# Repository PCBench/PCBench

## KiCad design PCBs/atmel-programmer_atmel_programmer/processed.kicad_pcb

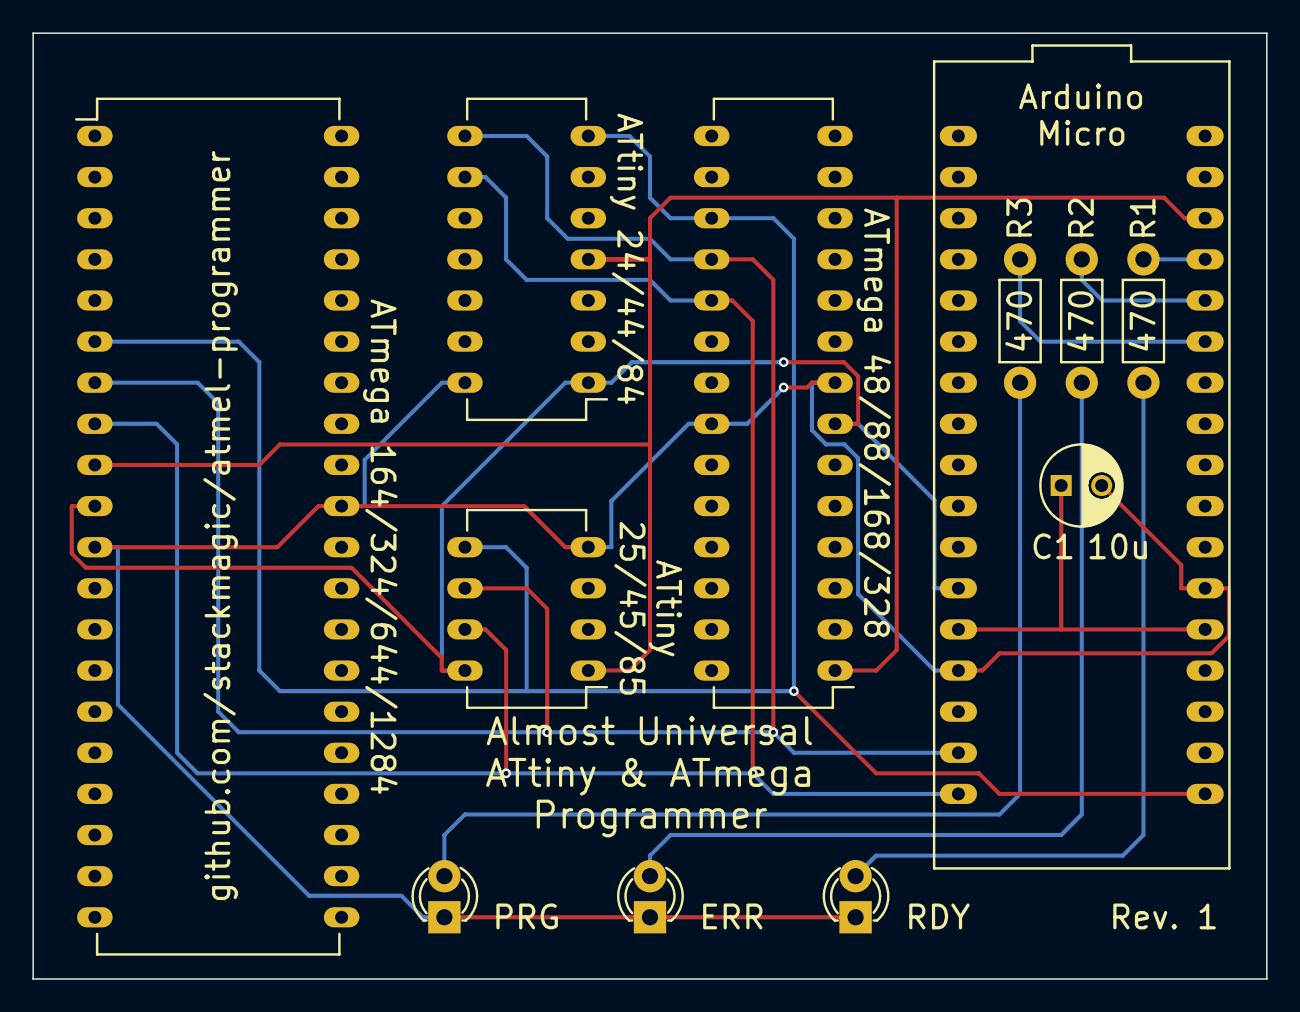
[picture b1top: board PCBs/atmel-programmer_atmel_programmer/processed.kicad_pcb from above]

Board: 2 copper layers, 76.2 x 58.4 mm, 12 parts (0 on the bottom side), 13 nets.

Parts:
C1: 10u; C_Radial_D5_L6_P2.5
D1, D2, D3: LED; LED-3MM
IC1: ATTINY85-P; DIP-8_W7.62mm_LongPads
IC2: ATTINY84-P; DIP-14_W7.62mm_LongPads
IC3: ATMEGA328-P; DIP-28_W7.62mm_LongPads
IC4: ATMEGA1284-P; DIP-40_W15.24mm_LongPads
R1, R2, R3: 470; Resistor_Horizontal_RM7mm
U1: Arduino_Micro_ISP; ArduinoMicro

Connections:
GND: C1.2, D1.1, D2.1, D3.1, IC1.4, IC2.14, IC3.8, IC3.22, IC4.11, IC4.31, U1.14, U1.23
MISO: IC1.6, IC2.8, IC3.18, IC4.7, U1.16
MOSI: IC1.5, IC2.7, IC3.17, IC4.6, U1.18
unnamed: C1.1, U1.13, U1.22
unnamed: D1.2, R1.1
unnamed: D2.2, R2.1
unnamed: D3.2, R3.1
unnamed: R1.2, U1.31
unnamed: R2.2, U1.30
unnamed: R3.2, U1.29
RST: IC1.1, IC2.4, IC3.1, IC4.9, U1.32
SCK: IC1.7, IC2.9, IC3.19, IC4.8, U1.17
VCC: IC1.8, IC2.1, IC3.7, IC4.10, U1.12

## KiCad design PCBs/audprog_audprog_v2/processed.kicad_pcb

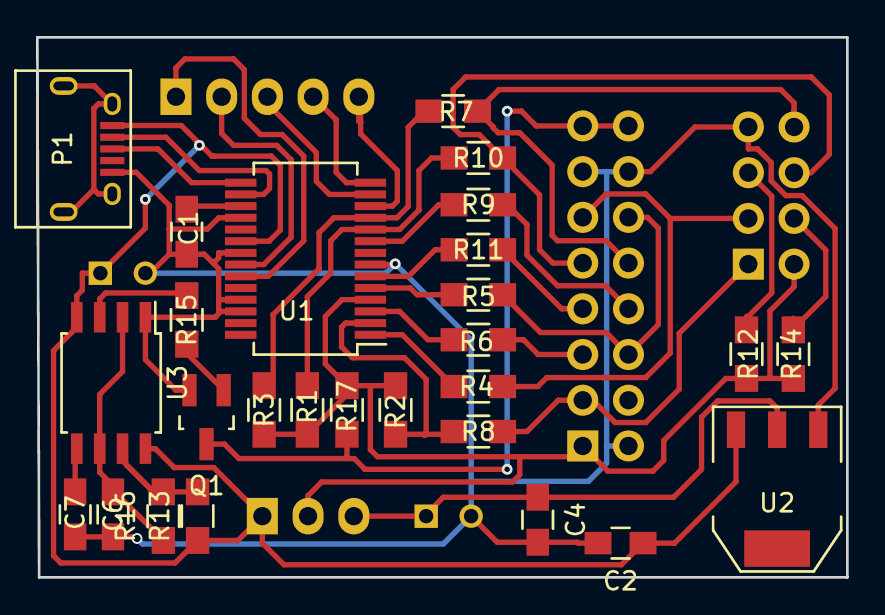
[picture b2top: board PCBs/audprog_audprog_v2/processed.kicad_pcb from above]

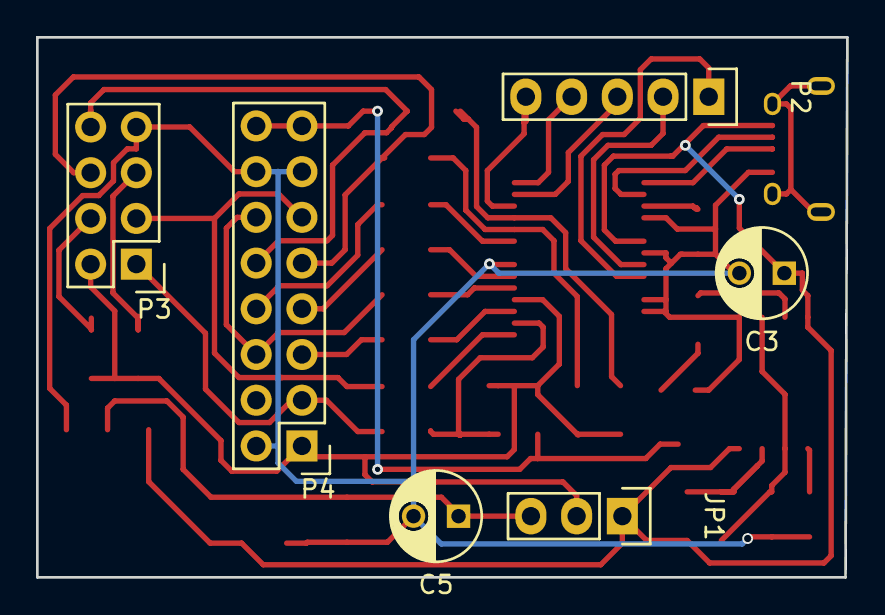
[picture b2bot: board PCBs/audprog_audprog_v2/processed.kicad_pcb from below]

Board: 2 copper layers, 45.0 x 30.0 mm, 33 parts (6 on the bottom side), 36 nets.

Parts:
C1, C6: 100n; C_0805_HandSoldering
C2, C4: 0,1u; C_0805_HandSoldering
C3, C5: 470u; C_Radial_D5_L11_P2.5
C7: 10n; C_0805_HandSoldering
JP1: Vcc_IO_SW; Pin_Header_Straight_1x03
P1: USB_OTG; USB_Micro-B
P2: CONN_01X05; Pin_Header_Straight_1x05
P3: CONN_02X04; Pin_Header_Straight_2x04
P4: CONN_02X08; Pin_Header_Straight_2x08
Q1: BC817; SOT-23_Handsoldering
R1, R2, R3: 5,6k; R_0805_HandSoldering
R4, R5, R6, R7, R8, R9, R10, R11: 22; R_0805_HandSoldering
R12, R14, R15, R17: 10k; R_0805_HandSoldering
R13: 1k; R_0805_HandSoldering
R16: 47,5k; R_0805_HandSoldering
U1: FT232RL; SSOP-28_5.3x10.2mm_Pitch0.65mm
U2: AP1117E33; SOT-223
U3: LM555N; SOIJ-8_5.3x5.3mm_Pitch1.27mm

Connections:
+3V3: C4.1, C5.1, JP1.3, U2.2
+5V: C2.1, C3.1, JP1.1, P1.1, R13.1, U1.20, U2.3, U3.4, U3.8
AUD_CK: P3.6, P4.9, R10.1
AUD_DATA0: P4.5, R6.1
AUD_DATA1: P4.6, P4.12, R5.1
AUD_DATA2: P4.7, R11.1
AUD_DATA3: P4.8, R9.1
AUD_RST: P3.1, P4.3, R8.1
AUD_SYNC: P3.8, P4.10, R7.1
BOOT_TX: P3.3, P4.11, R4.1
CBUS1: P2.1, U1.23
CBUS2: P2.2, U1.22
CBUS3: P2.3, U1.13
CBUS4: P2.4, U1.14
CBUS5: P2.5, U1.12
GND: C1.2, C2.2, C3.2, C4.2, C5.2, C6.2, C7.2, P1.5, P3.7, P4.2, P4.13, P4.14, Q1.2, U1.7, U1.18, U1.21, U1.25, U1.26, U2.1, U3.1
unnamed: C1.1, U1.17
unnamed: C6.1, R16.1, U3.2, U3.6
unnamed: C7.1, U3.5
unnamed: P1.2, U1.16
unnamed: P1.3, U1.15
unnamed: P3.4, R14.2
unnamed: P3.5, R12.1
unnamed: Q1.1, R15.1
unnamed: R1.2, R10.2, U1.10
unnamed: R2.2, R8.2, U1.2
unnamed: R3.2, R7.2, U1.11
unnamed: R4.2, U1.1
unnamed: R5.2, U1.5
unnamed: R6.2, U1.3
unnamed: R9.2, U1.9
unnamed: R11.2, U1.6
unnamed: R13.2, R16.2, U3.7
unnamed: R15.2, U3.3
VCC_IO: JP1.2, P3.2, P4.1, R1.1, R2.1, R3.1, R12.2, R14.1, R17.1, U1.4
WDT: P4.15, P4.16, Q1.3, R17.2

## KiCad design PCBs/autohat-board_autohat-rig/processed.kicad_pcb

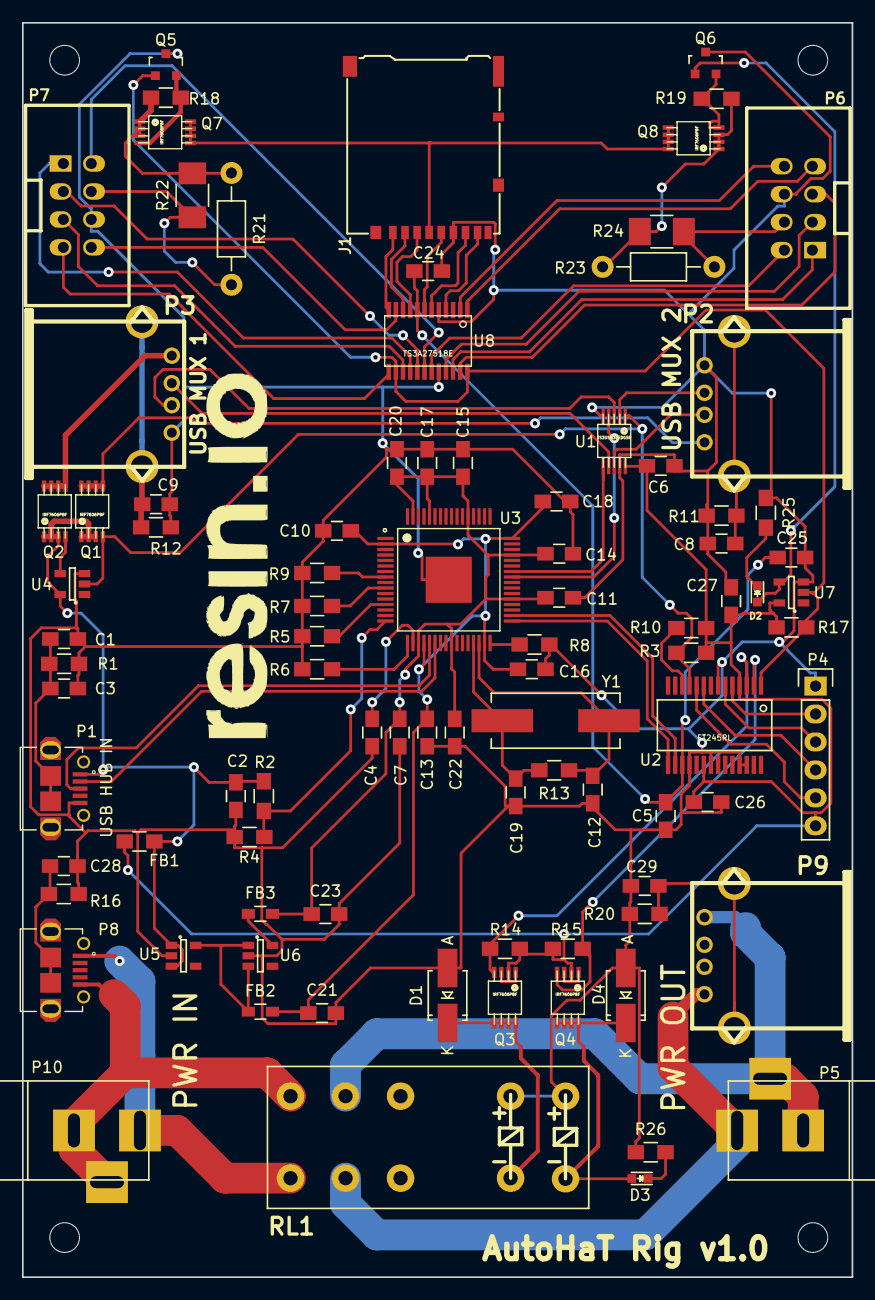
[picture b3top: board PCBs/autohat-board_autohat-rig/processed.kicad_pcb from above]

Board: 2 copper layers, 75.4 x 114.0 mm, 91 parts (0 on the bottom side), 78 nets.

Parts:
C1, C5, C6, C7, C10, C11, C13, C14, C15, C16, C17, C18, C20, C22, C24, C25, C26: 100n; C_0805_HandSoldering
C2, C21, C23: 10u; C_0805_HandSoldering
C3: 1n; C_0805_HandSoldering
C4: 1u; C_0805_HandSoldering
C8, C9, C28, C29: 27p; C_0805_HandSoldering
C12, C19: 18p; C_0805_HandSoldering
C27: 4.7u; C_0805_HandSoldering
D1, D4: ES1A-LTP; SMA_Handsoldering
D2, D3: LED; LED_0603
FB1: MI0805K400R-10; R_0805_HandSoldering
FB2, FB3: BLM18PG221SN1D; R_0603_HandSoldering
J1: USDCARD; HIROSE-MICROSD-DM3AT-SF
P1: USB HUB IN; TO_microUSB
P2: USB MUX 2; conn_usb_A
P3: USB MUX 1; conn_usb_A
P4: CONN_01X06; Pin_Header_Straight_1x06
P5, P10: BARREL_JACK
P6, P7: IDC_02X04; PSB_IDC_4x2
P8: PWR IN; TO_microUSB
P9: PWR OUT; conn_usb_A
Q1, Q2, Q3, Q4, Q7, Q8: IRF7606PBF; msoic-8
Q5, Q6: 2N7002; SOT-23
R1, R13: 1M; R_0805_HandSoldering
R2: 90.9K; R_0805_HandSoldering
R3, R4, R10, R14, R15, R17, R18, R19, R25, R26: 10K; R_0805_HandSoldering
R5, R6, R7, R9, R11, R12, R16, R20: 4.7K; R_0805_HandSoldering
R8: 9.53K; R_0805_HandSoldering
R21, R23: 0; Resistor_Horizontal_RM10mm
R22, R24: 0; R_1210_HandSoldering
RL1: G2RK-2-DC5; G2RK-2
U1: TS3USB30EDGSR; msoic-10
U2: FT245RL; ssop-28
U3: TUSB4041IPAPR; QFP50P1200X1200X105-65N
U4, U7: 74AHC1G14; SOT-23-5
U5: TLV73333; SOT-23-5
U6: TLV73311; SOT-23-5
U8: TS3A27518E; tssop-24
Y1: 24MHz; Crystal_HC49-SD_SMD

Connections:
+3V3: C5.1, C24.1, C25.1, U2.17, U8.8
/1P1V: FB3.1, U6.5
/3P3V: FB2.1, U5.5, U6.1, U6.3
/CLK_DUT: P6.5, U8.23
/CLK_TS: P7.5, U8.15
/CMD_DUT: P6.3, U8.21
/CMD_TS: P7.3, U8.17
/DAT0_DUT: P6.7, U8.1
/DAT0_TS: P7.7, U8.13
/DAT1_DUT: P6.8, U8.2
/DAT1_TS: P7.8, U8.11
/DAT2_DUT: P6.1, U8.22
/DAT2_TS: P7.1, U8.16
/DAT3_DUT: P6.2, U8.19
/DAT3_TS: P7.2, U8.18
/POWER_SW_OFF: Q3.4, R14.2, U2.3
/POWER_SW_ON: Q4.4, R15.2, U2.2
/SOCKET_SEL: Q5.1, R17.2, U2.1, U7.2, U8.14, U8.24
/USB_DN1+: U2.15, U3.33
/USB_DN1-: U2.16, U3.34
/USB_DN2+: U1.4, U3.41
/USB_DN2-: U1.6, U3.42
/USB_MUX1+: P2.3, U1.2
/USB_MUX1-: P2.2, U1.8
/USB_MUX2+: P3.3, U1.3
/USB_MUX2-: P3.2, U1.7
/USB_SEL: Q1.4, R3.2, U1.1, U2.11, U4.2
/USB_UP+: P1.3, U3.21
/USB_UP-: P1.2, U3.22
/USB_VBUS: C2.1, FB1.2, P1.1, Q1.1, Q1.2, Q1.3, Q2.1, Q2.2, Q2.3, R2.1, U4.5, U5.1, U5.3
/USD_VDD: J1.4, Q7.5, Q7.6, Q7.7, Q7.8, Q8.5, Q8.6, Q8.7, Q8.8
/VDD_DUT: P6.4, R23.1, R24.1
/VDD_TS: P7.4, R21.1, R22.1
/XI: C12.1, R13.1, U3.30, Y1.1
/XO: C19.1, R13.2, U3.29, Y1.2
GND: C1.2, C2.2, C3.2, C4.1, C5.2, C6.2, C7.2, C8.2, C9.2, C10.2, C11.2, C12.2, C13.2, C14.2, C15.2, C16.2, C17.2, C18.2, C19.2, C20.2, C21.2, C22.2, C23.2, C24.2, C25.2, C26.2, C27.2, C28.2, C29.2, D1.2, D4.2, J1.6, P1.5, P2.4, P3.4, P4.1, P6.6, P7.6, Q5.3, Q6.3, R1.1, R4.1, R5.1, R6.1, R7.1, R8.1, R9.1, R11.2, R12.2, R16.2, R20.2, R25.1, R26.1, RL1.9, RL1.10, U1.5, U1.9, U2.7, U2.18, U2.21, U2.25, U2.26, U3.65, U4.3, U5.2, U6.2, U7.3, U8.5, U8.20
unnamed: C1.1, C3.1, P1.6, R1.2
unnamed: C4.2, U3.18
unnamed: C8.1, P2.5, R11.1
unnamed: C9.1, P3.5, R12.1
unnamed: C10.1, C13.1, C16.1, C18.1, C21.1, FB2.2, U3.2, U3.20, U3.31, U3.48
unnamed: C7.1, C11.1, C14.1, C15.1, C17.1, C20.1, C22.1, C23.1, FB3.2, U3.19, U3.25, U3.37, U3.45, U3.53, U3.60, U3.63
unnamed: C28.1, P8.6, R16.1
unnamed: C29.1, P9.5, R20.1
unnamed: D1.1, Q3.5, Q3.6, Q3.7, Q3.8, RL1.2
unnamed: D2.1, R25.2
unnamed: D2.2, Q6.1, U7.4
unnamed: D3.1, R26.2
unnamed: D3.2, D4.1, Q4.5, Q4.6, Q4.7, Q4.8, RL1.1
unnamed: J1.1, U8.12
unnamed: J1.2, U8.10
unnamed: J1.3, U8.9
unnamed: J1.5, U8.7
unnamed: J1.7, U8.6
unnamed: J1.8, U8.4
unnamed: P2.1, Q1.5, Q1.6, Q1.7, Q1.8
unnamed: P3.1, Q2.5, Q2.6, Q2.7, Q2.8
unnamed: P4.2, U2.5
unnamed: P4.3, U2.6
unnamed: P4.4, U2.9
unnamed: P4.5, U2.10
unnamed: P5.1, P9.1, RL1.4
unnamed: P5.2, P5.3, P9.4, RL1.7
unnamed: P8.1, P10.1, RL1.5
unnamed: P8.5, P10.2, P10.3, RL1.6
unnamed: Q2.4, U4.4
unnamed: Q5.2, Q7.4, R18.2
unnamed: Q6.2, Q8.4, R19.2
unnamed: Q7.1, Q7.2, Q7.3, R18.1, R21.2, R22.2
unnamed: Q8.1, Q8.2, Q8.3, R19.1, R23.2, R24.2
unnamed: R2.2, R4.2, U3.16
unnamed: R5.2, U3.13
unnamed: R6.2, U3.17
unnamed: R7.2, U3.10
unnamed: R8.2, U3.32
unnamed: R9.2, U3.8
unnamed: R10.2, U2.12
VDD: C6.1, C26.1, C27.1, FB1.1, P4.6, Q3.1, Q3.2, Q3.3, Q4.1, Q4.2, Q4.3, R3.1, R10.1, R14.1, R15.1, R17.1, U1.10, U2.4, U2.20, U7.5

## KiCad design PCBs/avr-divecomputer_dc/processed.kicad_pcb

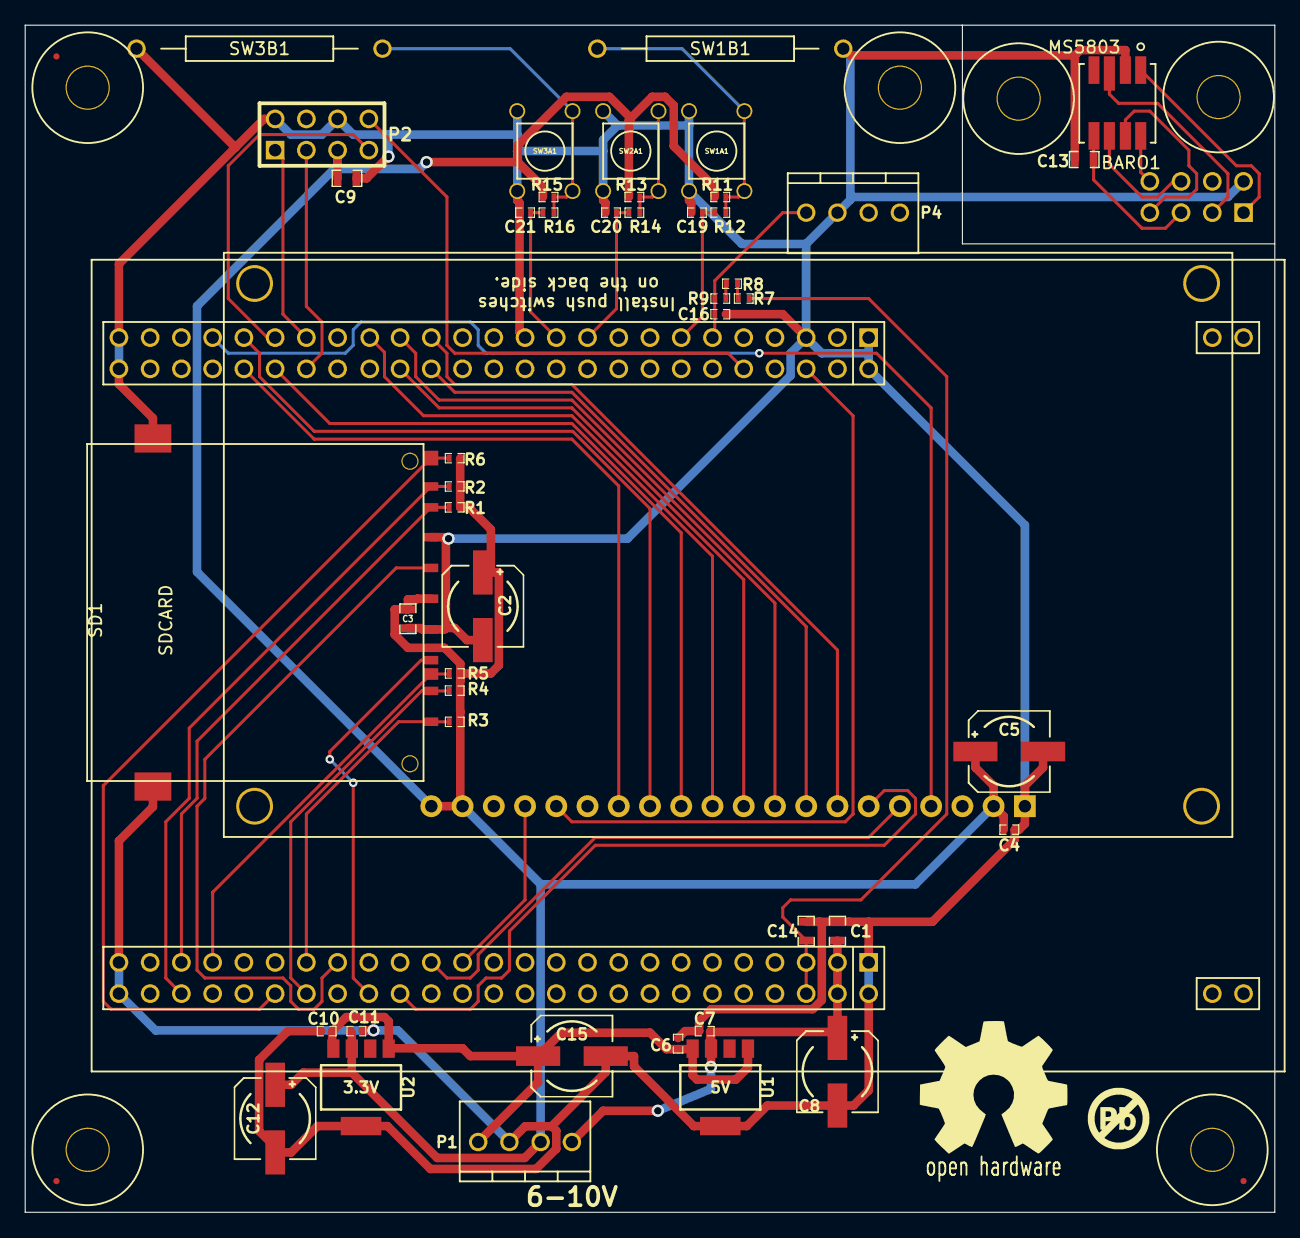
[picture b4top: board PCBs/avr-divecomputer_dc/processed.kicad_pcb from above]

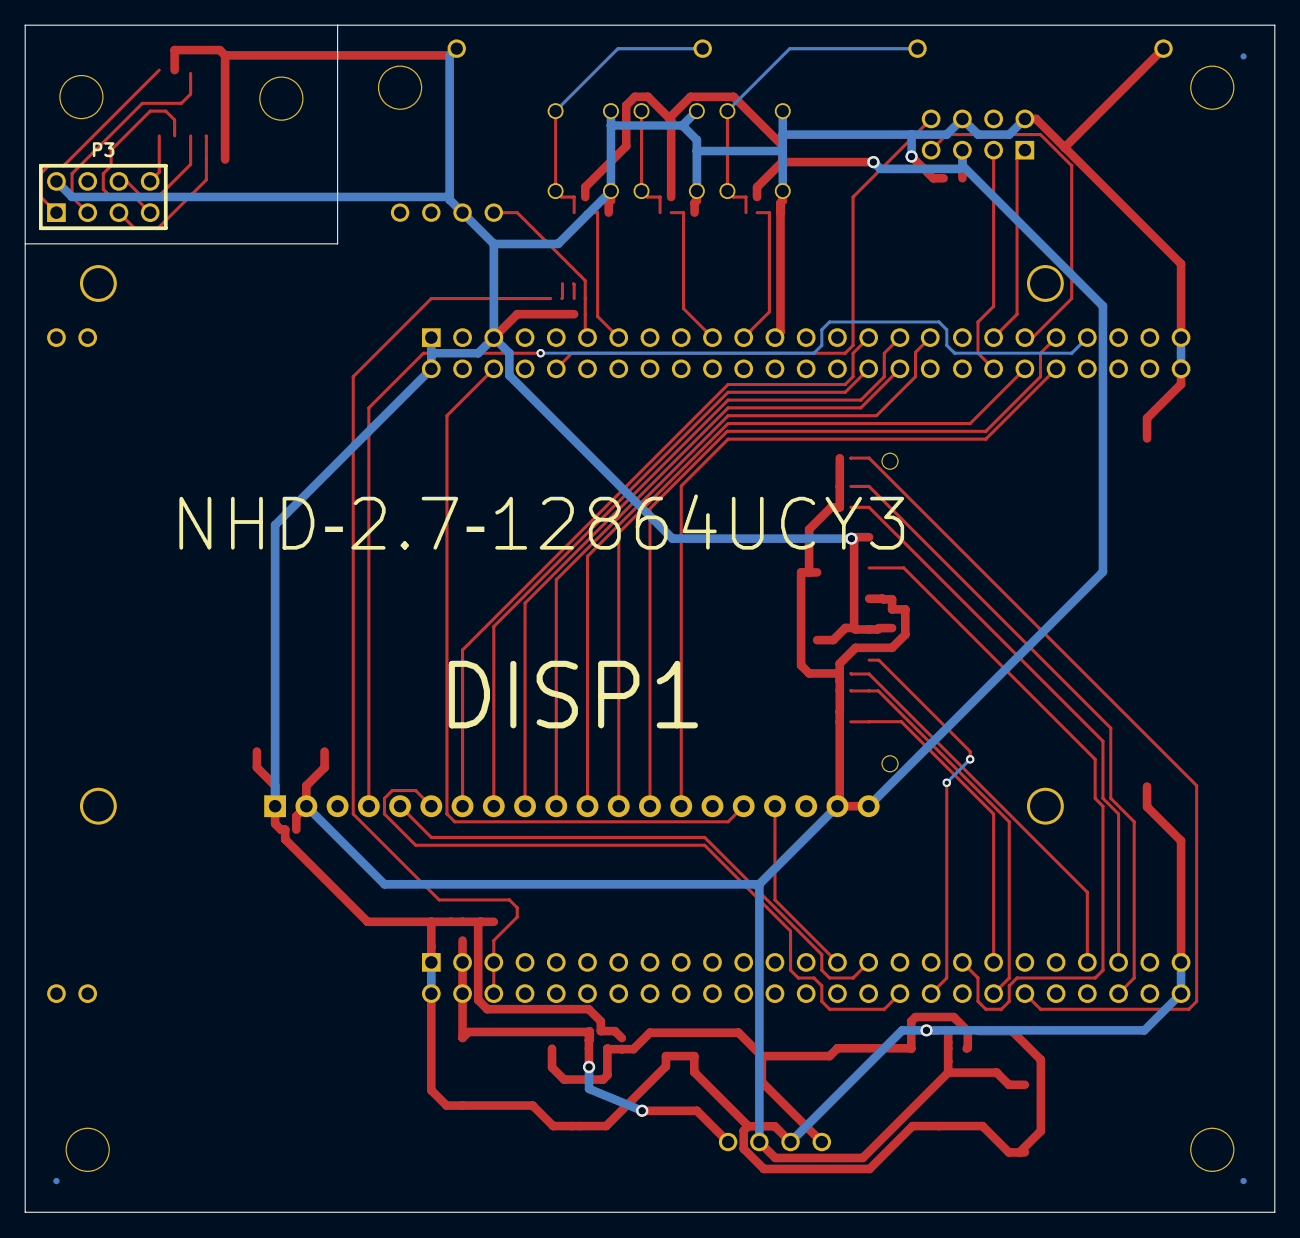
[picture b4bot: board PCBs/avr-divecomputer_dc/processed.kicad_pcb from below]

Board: 2 copper layers, 101.6 x 96.5 mm, 58 parts (2 on the bottom side), 45 nets.

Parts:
BARO1: MS5803
C1, C3, C9, C13, C14: 10uF; SM0603_Capa
C2, C5, C8, C12, C15: 150uF; c_elec_6.3x5.7
C4, C6, C7, C10, C11, C16, C19, C20, C21: 1uF; SM0402_c
DISP1: NHD‐2.7‐12864UCY3
FID1: FID**; FIDUCIAL
FID2, FID3: VAL**; FIDUCIAL
J1: STM32F4_DISCOVERY_HEADER; stm32f4_discovery_header
M3_MOUNT, M3_MOUNT_2, M3_MOUNT_3, M3_MOUNT_4, M3_MOUNT_5, M3_MOUNT_6: VAL**; M3_MOUNT
P1, P4: CONN_4; ED10563-ND
P2, P3: CONN_4X2; pin_array_4x2
R1, R2, R3, R4, R5, R6, R7, R8, R9, R11, R12, R13, R14, R15, R16: 100k; SM0402
SD1: SDCARD; 101-00405-75-ND
SW1A1, SW2A1, SW3A1: SW_PUSH; P8008S-ND
SW1B1, SW3B1: SW_PUSH; REED
U1: 5V; SOT-223-5
U2: 3.3V; SOT-223-5

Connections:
+3.3V: C2.1, C3.1, C4.1, C5.1, C9.1, C11.1, C12.1, DISP1.2, DISP1.19, DISP1.20, P1.3, P2.5, R1.1, R2.1, R3.1, R4.1, R5.2, R6.2, R11.2, R13.2, R15.2, SD1.4, U2.3
+5V: C1.1, C7.1, C8.1, J1.97, J1.98, P1.4, U1.3
+BATT: C6.1, C10.1, C15.1, P1.1, U1.1, U1.4, U2.1, U2.4
DEPTH_CS: J1.38, P2.3
FSMC_A16: DISP1.4, J1.43
FSMC_D08: DISP1.7, J1.29
FSMC_D09: DISP1.8, J1.30
FSMC_D10: DISP1.9, J1.31
FSMC_D11: DISP1.10, J1.32
FSMC_D12: DISP1.11, J1.33
FSMC_D13: DISP1.12, J1.40
FSMC_D14: DISP1.13, J1.41
FSMC_D15: DISP1.14, J1.42
FSMC_NE1: DISP1.17, J1.73
FSMC_NOE: DISP1.6, J1.70
FSMC_NWE: DISP1.5, J1.71
GND: BARO1.2, C1.2, C2.2, C3.2, C4.2, C5.2, C6.2, C7.2, C8.2, C9.2, C10.2, C11.2, C12.2, C13.2, C14.2, C15.2, C16.2, C19.2, C20.2, C21.2, DISP1.1, J1.1, J1.2, J1.5, J1.23, J1.49, J1.50, J1.51, J1.52, J1.99, J1.100, P1.2, P2.2, P2.6, P3.2, P4.3, SD1.3, SD1.6, SD1.10, SW1A1.1, SW1B1.1, SW2A1.1, SW3A1.1, SW3B1.1, U1.5, U2.5
unnamed: R11.1, R12.1, SW1A1.2, SW1B1.2
unnamed: R7.1, R8.2
unnamed: R8.1, R9.1
unnamed: R13.1, R14.1, SW2A1.2
unnamed: R15.1, R16.1, SW3A1.2, SW3B1.2
unnamed: BARO1.8, P3.8
unnamed: BARO1.7, P3.7
unnamed: BARO1.6, P3.6
unnamed: BARO1.5, C13.1, P3.5
unnamed: BARO1.1, P3.1
unnamed: BARO1.3, P3.3
RESET: DISP1.16, J1.6
SDIO_CK: J1.65, SD1.5
SDIO_CMD: J1.68, SD1.2
SDIO_D0: J1.55, R1.2, SD1.7
SDIO_D1: J1.56, R2.2, SD1.8
SDIO_D2: J1.63, R3.2, SD1.9
SDIO_D3: J1.64, R4.2, SD1.1
SD_CD: J1.57, R5.1, SD1.11
SD_WP: J1.62, R6.1, SD1.12
SPI2_MISO: J1.10, P2.8
SPI2_MOSI: J1.39, P2.7
SPI2_SCK: J1.37, P2.1
STM_3V: C14.1, J1.95, J1.96, R7.2
SW1: C19.1, J1.13, R12.2
SW2: C20.1, J1.19, R14.2
SW3: C21.1, J1.21, R16.2
WATER: C16.1, J1.11, P4.4, R9.2

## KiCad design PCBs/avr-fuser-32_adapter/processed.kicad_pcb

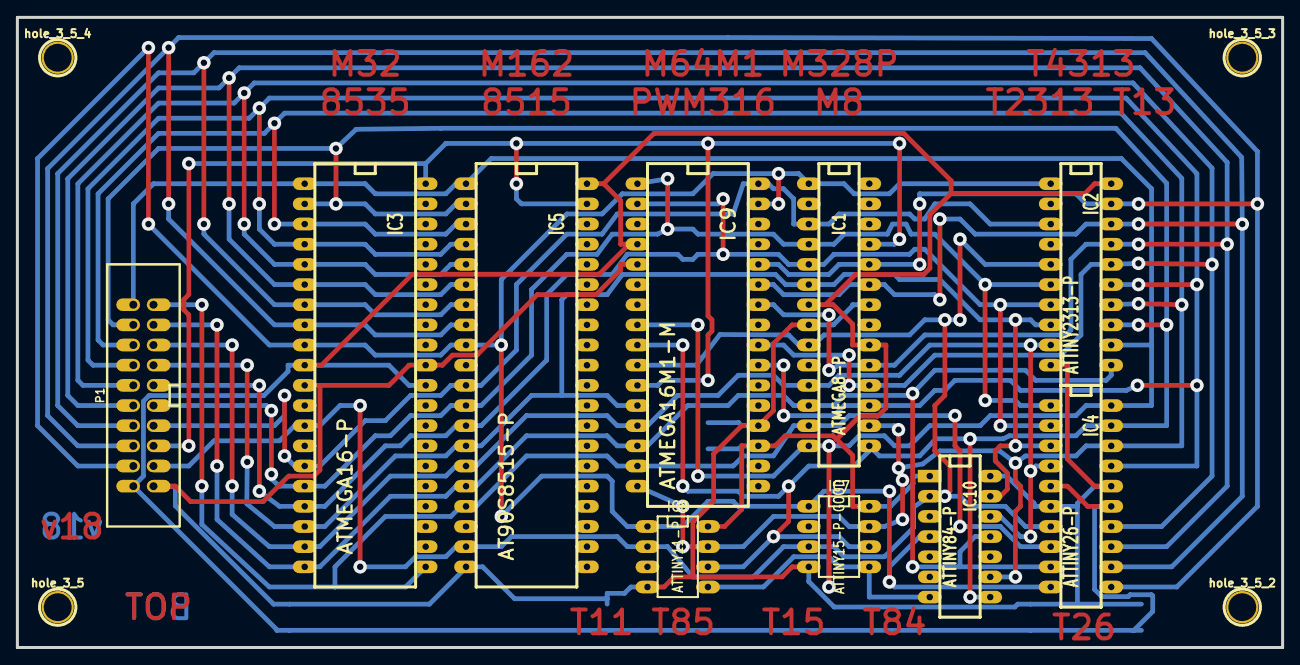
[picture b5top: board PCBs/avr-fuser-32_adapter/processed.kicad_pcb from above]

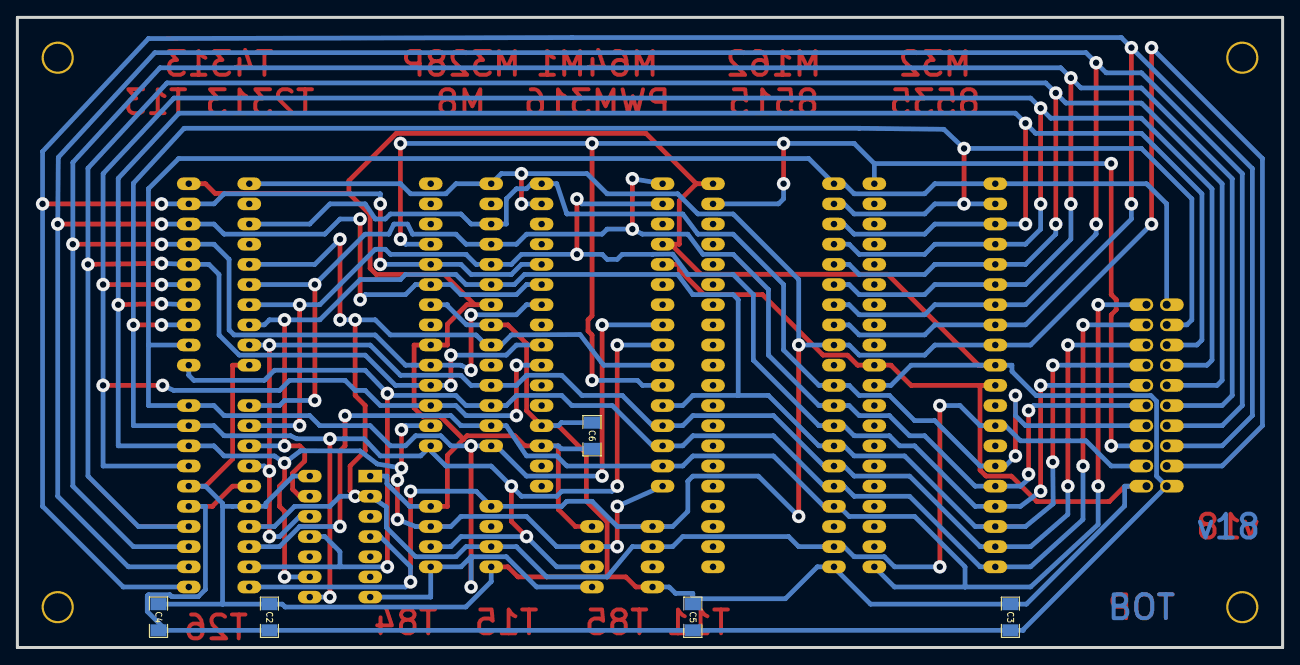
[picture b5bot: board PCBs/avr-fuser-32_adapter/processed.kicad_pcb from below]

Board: 2 copper layers, 159.4 x 79.4 mm, 19 parts (5 on the bottom side), 20 nets.

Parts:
C2, C3, C4, C5, C6: 10nF; SM1206
IC1: ATMEGA8-P; DIP-28__300-bigpads
IC2: ATTINY2313-P; DIP-20__300-bigpads
IC3: ATMEGA16-P; DIP-40__600-bigpads
IC4: ATTINY26-P; DIP-20__300-bigpads
IC5: AT90S8515-P; DIP-40__600-bigpads
IC7: ATTINY15-P-GOOD; DIP-8__300-bigpads
IC8: ATTINY11-P; DIP-8__300-bigpads
IC9: ATMEGA16M1-M; DIP-32__600_bigpads
IC10: ATTINY84-P; DIP-14__300_ELL-bigpads
P1: CONN_10X2; conn_strip_10x2_largepads
hole_3_5, hole_3_5_2, hole_3_5_3, hole_3_5_4: 3.5mm; hole_3_5

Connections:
/BS1: IC1.6, IC2.8, IC3.18, IC4.3, IC5.14, IC9.12, IC10.13, P1.13
/BS2: IC1.25, IC3.40, IC5.39, IC9.11, P1.5
/CLK: IC1.9, IC2.5, IC3.13, IC4.7, IC5.19, IC7.3, IC8.2, IC9.10, IC10.2, P1.3
/D0: IC1.14, IC2.12, IC3.1, IC4.20, IC5.1, IC7.5, IC8.5, IC9.8, IC10.7, P1.20
/D1: IC1.15, IC2.13, IC3.2, IC4.19, IC5.2, IC7.6, IC8.6, IC9.9, IC10.8, P1.18
/D2: IC1.16, IC2.14, IC3.3, IC4.18, IC5.3, IC7.7, IC8.7, IC9.16, IC10.9, P1.16
/D3: IC1.17, IC2.15, IC3.4, IC4.17, IC5.4, IC9.23, P1.14
/D4: IC1.18, IC2.16, IC3.5, IC4.14, IC5.5, IC9.24, P1.12
/D5: IC1.19, IC2.17, IC3.6, IC4.13, IC5.6, IC9.26, P1.10
/D6: IC1.23, IC2.18, IC3.7, IC4.12, IC5.7, IC9.27, P1.8
/D7: IC1.24, IC2.19, IC3.8, IC4.11, IC5.8, IC9.28, P1.6
/OE: IC1.4, IC2.6, IC3.16, IC4.1, IC5.12, IC9.1, P1.9
/PAGEL: IC1.13, IC3.21, IC4.8, IC5.17, IC9.15, P1.19
/RDY: IC1.3, IC2.3, IC3.15, IC5.11, IC9.32, P1.7
/RST12V: IC1.1, IC2.1, IC3.9, IC4.10, IC5.9, IC7.1, IC8.1, IC9.31, IC10.4, P1.4
/VCC: C2.1, C3.1, C4.1, C5.1, C6.1, IC1.7, IC1.20, IC2.20, IC3.10, IC3.30, IC4.5, IC4.15, IC5.40, IC7.8, IC8.8, IC9.4, IC9.19, IC10.1, P1.2
/WR: IC1.5, IC2.7, IC3.17, IC4.2, IC5.13, IC9.2, P1.11
/XA0: IC1.11, IC2.9, IC3.19, IC4.4, IC5.15, IC9.13, IC10.12, P1.15
/XA1: IC1.12, IC2.11, IC3.20, IC4.9, IC5.16, IC9.14, IC10.11, P1.17
GND: C2.2, C3.2, C4.2, C5.2, C6.2, IC1.8, IC1.22, IC2.10, IC3.11, IC3.31, IC4.6, IC4.16, IC5.20, IC7.4, IC8.4, IC9.5, IC9.20, IC10.14, P1.1

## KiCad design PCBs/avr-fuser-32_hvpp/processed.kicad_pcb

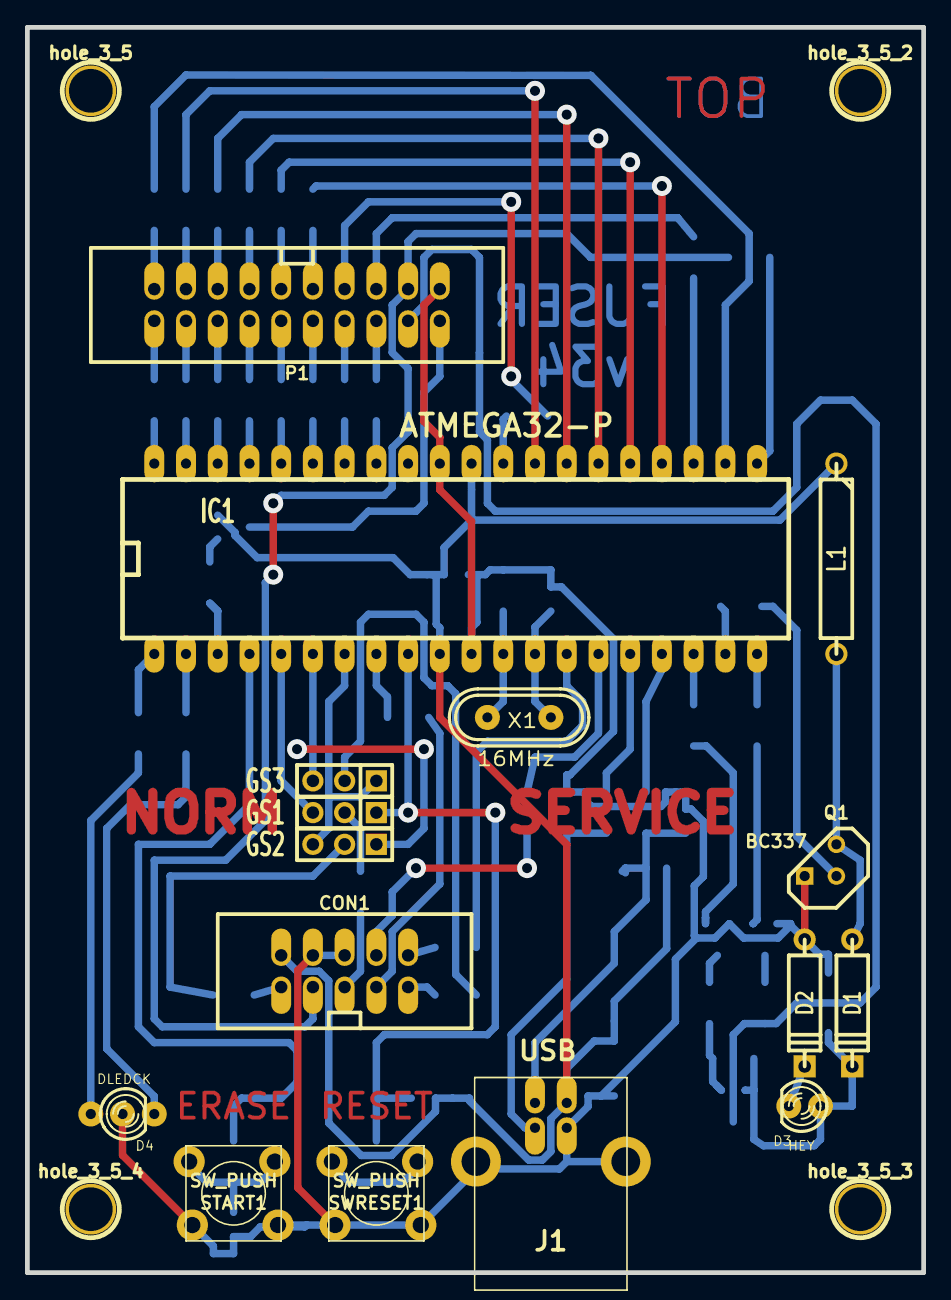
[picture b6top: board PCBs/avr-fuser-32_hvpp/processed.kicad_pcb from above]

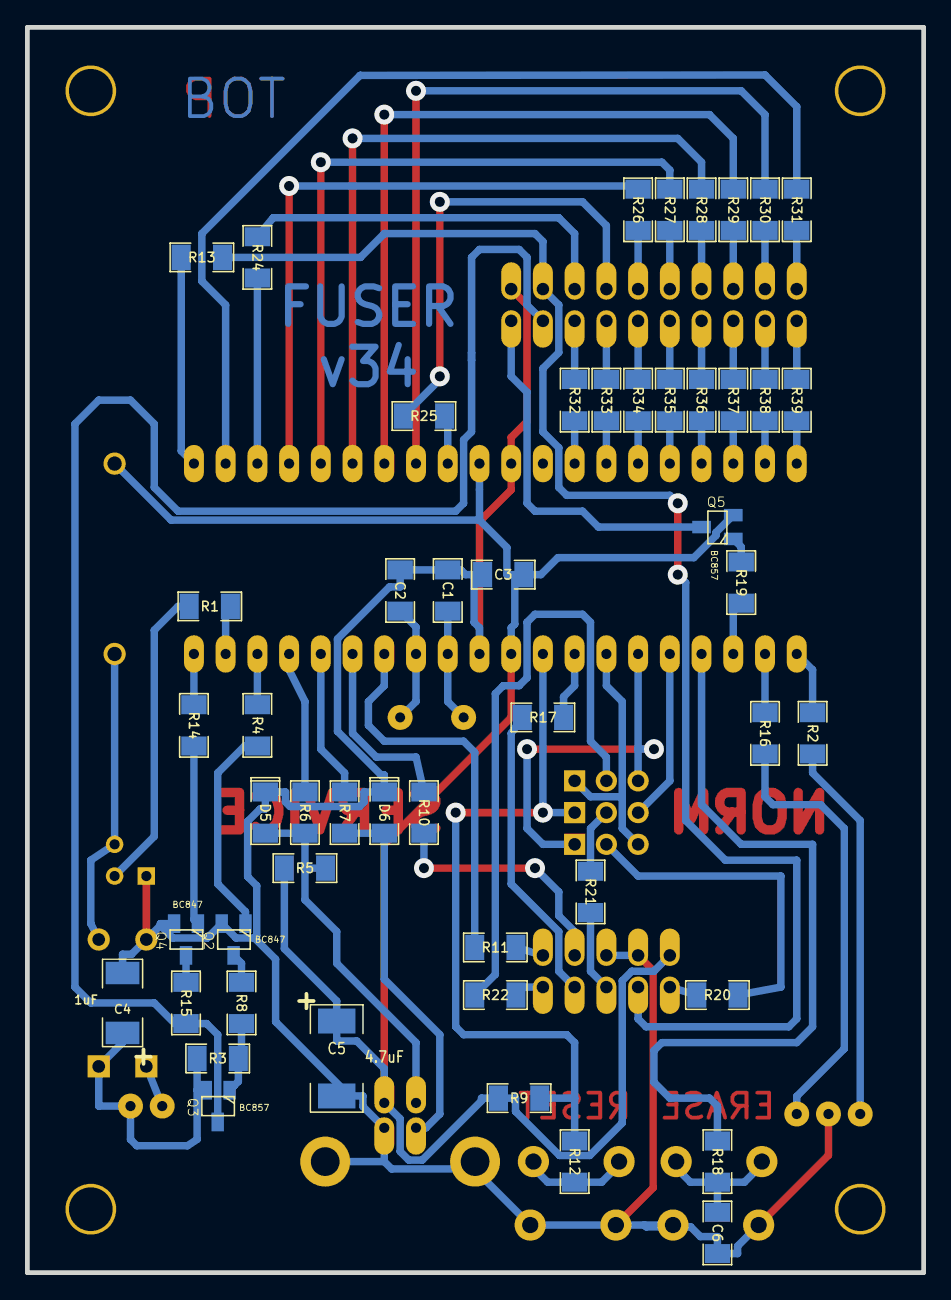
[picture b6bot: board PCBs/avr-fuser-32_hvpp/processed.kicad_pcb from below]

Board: 2 copper layers, 71.8 x 99.7 mm, 70 parts (50 on the bottom side), 81 nets.

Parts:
C1, C2: 18pF; SM1206
C3: 56nF; SM1206
C4: 1uF; SM2010
C5: 4.7uF; SM2512
C6: 1nF; SM1206
CON1: AVR-ISP-10; conn_strip_5x2_largepads
D1: BAT42; D4
D2: 10V; D4
D3: HEY; LED-3MM-bigpads
D4: DLEDCK; LED-3MM-dual-bigpads
D5, D6: 3.6V; SM1206POL
GS1, GS2, GS3: GS3; SIL-3_bigpads
IC1: ATMEGA32-P; DIP-40__600-bigpads
J1: USB; USB_B-bigpads
L1: 220uH; R6
P1: CONN_10X2; conn_strip_10x2_largepads
Q1: BC337; TO92
Q2, Q4: BC847; SOT23_INV-bigpads
Q3, Q5: BC857; SOT23_INV-bigpads
R1: 9.1k; SM1206
R2, R4, R14, R16, R19: 1k; SM1206
R3: 100k; SM1206
R5: 2.2k; SM1206
R6, R7: 68; SM1206
R8: 4.7k; SM1206
R9: 15k; SM1206
R10, R11, R13, R17, R20, R21, R22, R24, R25, R26, R27, R28, R29, R30, R31, R32, R33, R34, R35, R36, R37, R38, R39: 330; SM1206
R12, R15, R18: 470; SM1206
START1: SW_PUSH; SW_PUSH_BIGHOLE
SWRESET1: SW_PUSH; SW_PUSH_BIGHOLE
X1: 16MHz; crystal_hc-49s
hole_3_5, hole_3_5_2, hole_3_5_3, hole_3_5_4: 3.5mm; hole_3_5

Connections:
+5V: C3.1, C5.1, CON1.2, IC1.10, IC1.30, J1.1, L1.1, Q5.1, R5.2, R9.2
+12V: C4.1, D1.2, D3.1, Q3.1, R3.1
/BS1: IC1.26, R28.2
/BS1_A: P1.13, R28.1
/BS2: IC1.23, R24.2
/BS2_A: P1.5, R24.1
/CLK: IC1.21, R13.2
/CLK_A: CON1.3, P1.3, R13.1
/D0: IC1.40, R39.1
/D0_A: P1.20, R39.2
/D1: IC1.39, R38.1
/D1_A: P1.18, R38.2
/D2: IC1.38, R37.1
/D2_A: P1.16, R37.2
/D3: IC1.37, R36.1
/D3_A: P1.14, R36.2
/D4: IC1.36, R35.1
/D4_A: P1.12, R35.2
/D5: IC1.35, R34.1
/D5_A: P1.10, R34.2
/D6: IC1.34, R33.1
/D6_A: P1.8, R33.2
/D7: IC1.33, R32.1
/D7_A: P1.6, R32.2
/D+: D6.2, J1.3, R7.1
/D-: D5.2, J1.2, R5.1, R6.1
/FLYBACK: D1.1, L1.2, Q1.3
/LEDG: D4.3, R16.2
/LEDGREEN: IC1.2, R16.1
/LEDR: D4.1, R2.2
/LEDRED: IC1.1, R2.1
/LVC: Q4.3, R15.2
/MISO: GS2.3, GS3.1, IC1.7
/MISO_A: CON1.9, R22.1
/MISO_B: GS3.2, R22.2
/MOSI: GS2.1, GS3.3, IC1.6
/MOSI_A: CON1.1, R20.1
/MOSI_B: GS2.2, R20.2
/NPNBH: Q2.2, R4.1
/NPNBL: Q4.2, R14.1
/NPNCH: Q2.3, R8.2
/OE: IC1.24, R26.2
/OE_A: P1.9, R26.1
/PAGEL: IC1.22, R31.2
/PAGEL_A: P1.19, R31.1
/PNPBH: Q3.2, R3.2, R8.1
/PWM: IC1.19, R1.1
/PWMB: Q1.2, R1.2
/RDY: IC1.29, R25.2
/RDY_A: P1.7, R25.1
/RESET: GS1.1, IC1.9, R9.1, R12.1
/RESETBTN: R12.2, SWRESET1.2
/RST: GS1.3, IC1.5
/RST12V: P1.4, Q3.3, R15.1
/RSTH: IC1.18, R4.2
/RSTL: IC1.20, R14.2
/RST_A: CON1.5, R21.1
/RST_B: GS1.2, R21.2
/RXD: IC1.14, R11.1
/RXD_A: CON1.10, R11.2
/SCK: IC1.8, R17.2
/SCK_A: CON1.7, R17.1
/START: IC1.4, R18.1
/STARTBTN: C6.1, R18.2, START1.2
/TXD: IC1.15, R10.1
/TXD_A: CON1.8, R10.2
/VCC: P1.2, Q5.3
/VCCB: Q5.2, R19.1
/VD+: IC1.16, R7.2
/VD-: IC1.17, R6.2
/WR: IC1.25, R27.2
/WR_A: P1.11, R27.1
/XA0: IC1.27, R29.2
/XA0_A: P1.15, R29.1
/XA1: IC1.28, R30.2
/XA1_A: P1.17, R30.1
/ZV: D2.2, D3.2
/nVCC: IC1.3, R19.2
GND: C1.1, C2.1, C3.2, C4.2, C5.2, C6.2, CON1.4, CON1.6, D2.1, D4.2, D5.1, D6.1, IC1.11, IC1.31, J1.4, J1.5, J1.6, P1.1, Q1.1, Q2.1, Q4.1, START1.1, SWRESET1.1
unnamed: C1.2, IC1.12, X1.2
unnamed: C2.2, IC1.13, X1.1

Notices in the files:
PCBs/autohat-board_autohat-rig/processed.kicad_pcb:
Copyright (c) 2016 Samsung Electronics Co., Ltd All Rights Reserved
